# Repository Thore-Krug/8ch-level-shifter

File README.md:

# 8ch-level-shifter
Simple 8-Channel Level Shifter with castellated edges

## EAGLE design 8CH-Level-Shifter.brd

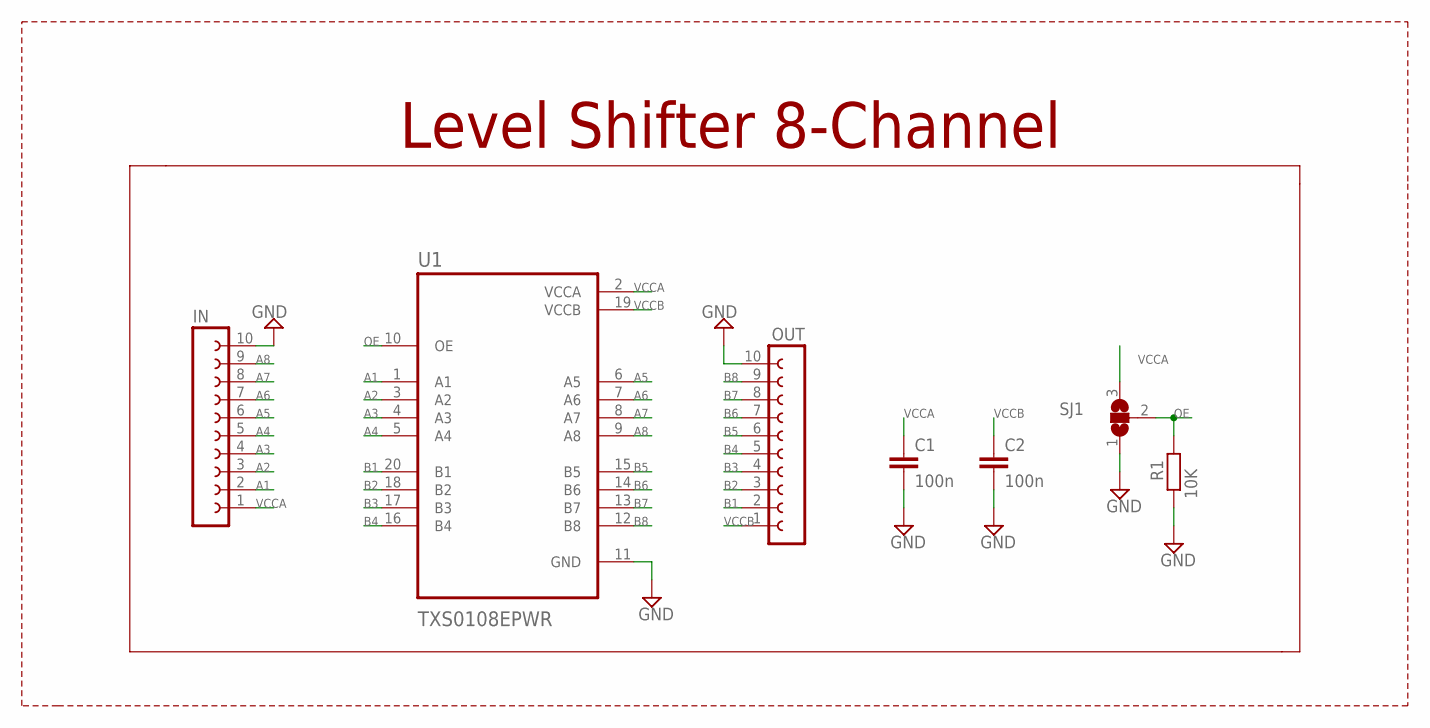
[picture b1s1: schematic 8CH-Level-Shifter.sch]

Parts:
C1, C2: 100n; C0805
IN: CON-LSTA_FE10-1; CON-LSTA_FE10
OUT: CON-LSTA_FE10-1; CON-LSTA_FE10
R1: 10K; R0805
SJ1: SJ2W; SJ_2
U1: TXS0108EPWR; SOP65P640X120-20N

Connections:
A1: IN.2, U1.1 (A1)
A2: IN.3, U1.3 (A2)
A3: IN.4, U1.4 (A3)
A4: IN.5, U1.5 (A4)
A5: IN.6, U1.6 (A5)
A6: IN.7, U1.7 (A6)
A7: IN.8, U1.8 (A7)
A8: IN.9, U1.9 (A8)
B1: OUT.2, U1.20 (B1)
B2: OUT.3, U1.18 (B2)
B3: OUT.4, U1.17 (B3)
B4: OUT.5, U1.16 (B4)
B5: OUT.6, U1.15 (B5)
B6: OUT.7, U1.14 (B6)
B7: OUT.8, U1.13 (B7)
B8: OUT.9, U1.12 (B8)
GND: C1.2, C2.2, IN.10, OUT.10, R1.1, SJ1.1, U1.11 (GND)
OE: R1.2, SJ1.2, U1.10 (OE)
VCCA: C1.1, IN.1, SJ1.3, U1.2 (VCCA)
VCCB: C2.1, OUT.1, U1.19 (VCCB)

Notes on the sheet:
Level Shifter 8-Channel

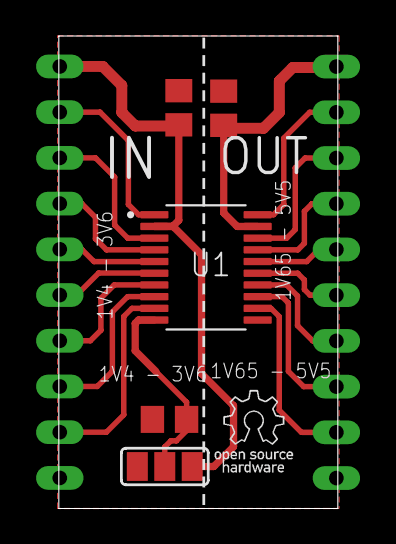
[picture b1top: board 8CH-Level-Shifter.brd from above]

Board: 2 copper layers, 15.5 x 26.2 mm, 7 parts (0 on the bottom side), 20 nets.

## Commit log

2020-11-16 Addition of Board files.
    Signed off by: Thore Krug opensource[at]thorekrug.de
